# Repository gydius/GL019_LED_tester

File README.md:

# GL019_LED_tester

A simple PCB to test SMD LEDs. Solder your SMD LEDs and add an adaquate resitor to it and you will be able to choose quickly the right couple LED/R for your next project ! 

I did it since I do have quite a lot of references of SMD LEDs in my personnal stock so I would forget what color they are. 

For time for me with sending custom panel to a manufacturer, everything went nice. Used [GitHub - ThisIsNotRocketScience/GerberTools: Tools to load/edit/create/panelizer sets of gerber files](https://github.com/ThisIsNotRocketScience/GerberTools)

# This project is still in progress !

This is the first revision, I got the PCBs from JLC and they're nice !

But there a few mistakes and changes to do for next revision : 

- Change the solderjump for a bigger one.  Might also chage by a 1x2 2.54mm connector and 2.54mm jumper. 

- Get the 0402 and 0804 LEDs on same footprint (and might also add THT LEDs)

- Same but for 0402 and 0804 SMD resistors 

- Increase the maring sikscreen area, it is currently not enough to easily write the LEDs' references on it. 

- Add silkscreen to right S/N off the PCB.

- Change the silkscreen color, the blue is definitey not wise when you want to write on it with black/blue permanent marker. Might try white FR4 with black silkscreen. 

Few photos :

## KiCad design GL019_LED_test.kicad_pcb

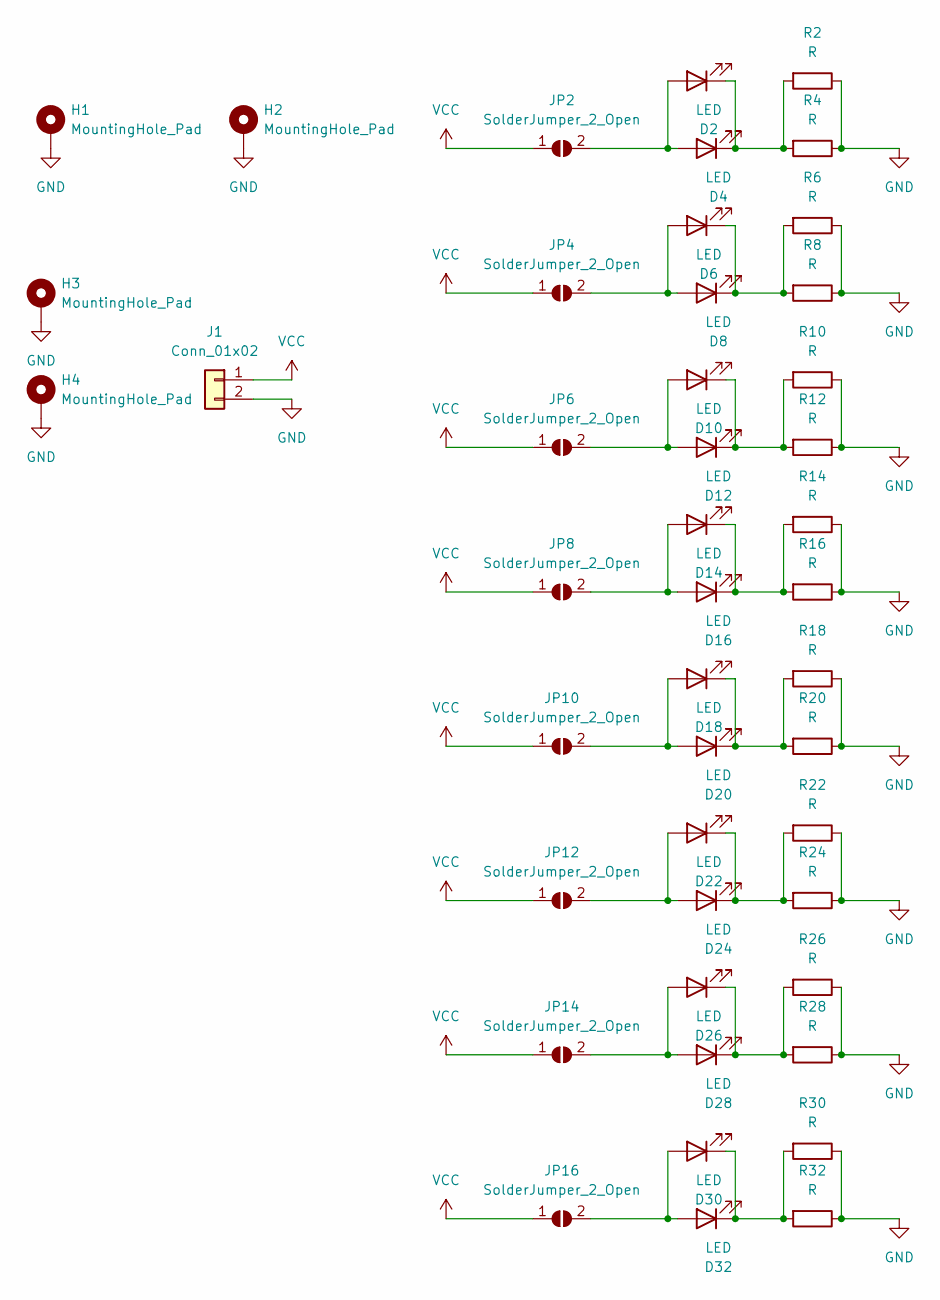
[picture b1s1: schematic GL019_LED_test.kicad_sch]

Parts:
D2, D6, D10, D14, D18, D22, D26, D30: LED; LED_0603_1608Metric_Pad1.05x0.95mm_HandSolder
D4, D8, D12, D16, D20, D24, D28, D32: LED; LED_0805_2012Metric_Pad1.15x1.40mm_HandSolder
H1, H2, H3, H4: MountingHole_Pad; MountingHole_3.2mm_M3_Pad_Via
J1: Conn_01x02; TerminalBlock_bornier-2_P5.08mm
JP2, JP4, JP6, JP8, JP10, JP12, JP14, JP16: SolderJumper_2_Open; SolderJumper-2_P1.3mm_Open_RoundedPad1.0x1.5mm
R2, R6, R10, R14, R18, R22, R26, R30: R; R_0603_1608Metric_Pad0.98x0.95mm_HandSolder
R4, R8, R12, R16, R20, R24, R28, R32: R; R_0805_2012Metric_Pad1.20x1.40mm_HandSolder

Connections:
GND: H1.1, H2.1, H3.1, H4.1, J1.2, R2.1, R4.1, R6.1, R8.1, R10.1, R12.1, R14.1, R16.1, R18.1, R20.1, R22.1, R24.1, R26.1, R28.1, R30.1, R32.1
unnamed: D2.1 (K), D4.1 (K), R2.2, R4.2
unnamed: D2.2 (A), D4.2 (A), JP2.2 (B)
unnamed: D6.1 (K), D8.1 (K), R6.2, R8.2
unnamed: D6.2 (A), D8.2 (A), JP4.2 (B)
unnamed: D10.1 (K), D12.1 (K), R10.2, R12.2
unnamed: D10.2 (A), D12.2 (A), JP6.2 (B)
unnamed: D14.1 (K), D16.1 (K), R14.2, R16.2
unnamed: D14.2 (A), D16.2 (A), JP8.2 (B)
unnamed: D18.1 (K), D20.1 (K), R18.2, R20.2
unnamed: D18.2 (A), D20.2 (A), JP10.2 (B)
unnamed: D22.1 (K), D24.1 (K), R22.2, R24.2
unnamed: D22.2 (A), D24.2 (A), JP12.2 (B)
unnamed: D26.1 (K), D28.1 (K), R26.2, R28.2
unnamed: D26.2 (A), D28.2 (A), JP14.2 (B)
unnamed: D30.1 (K), D32.1 (K), R30.2, R32.2
unnamed: D30.2 (A), D32.2 (A), JP16.2 (B)
VCC: J1.1, JP2.1 (A), JP4.1 (A), JP6.1 (A), JP8.1 (A), JP10.1 (A), JP12.1 (A), JP14.1 (A), JP16.1 (A)

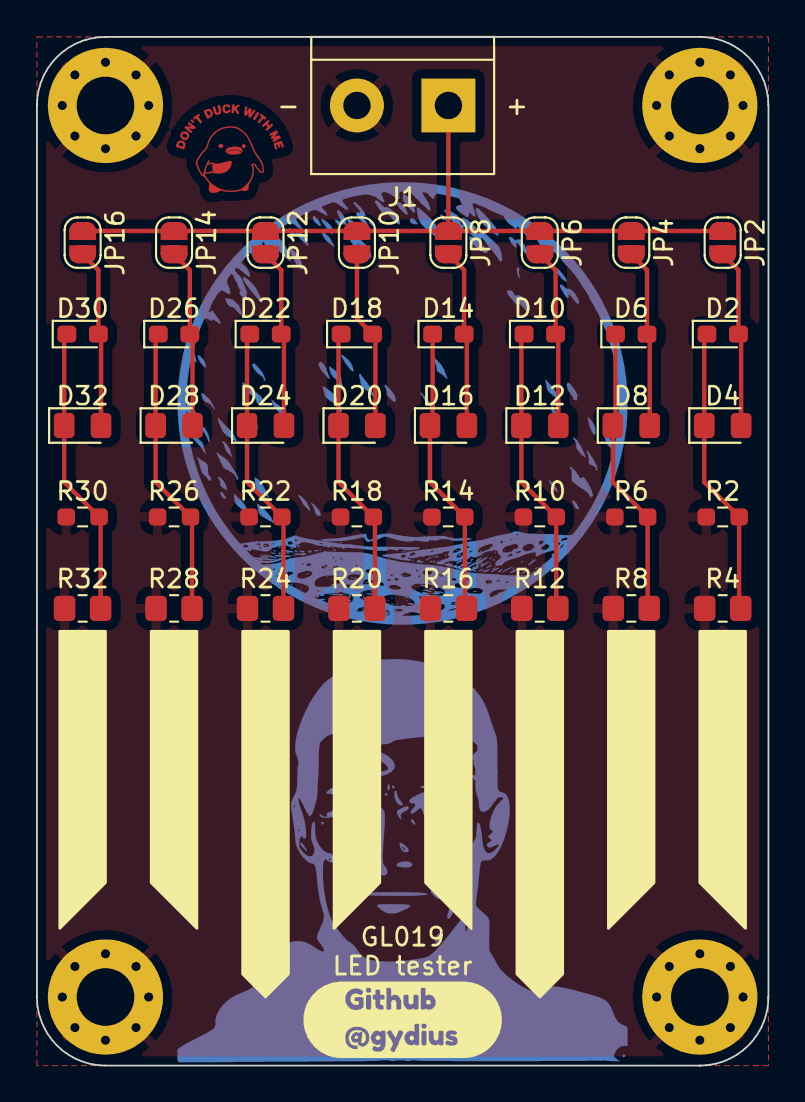
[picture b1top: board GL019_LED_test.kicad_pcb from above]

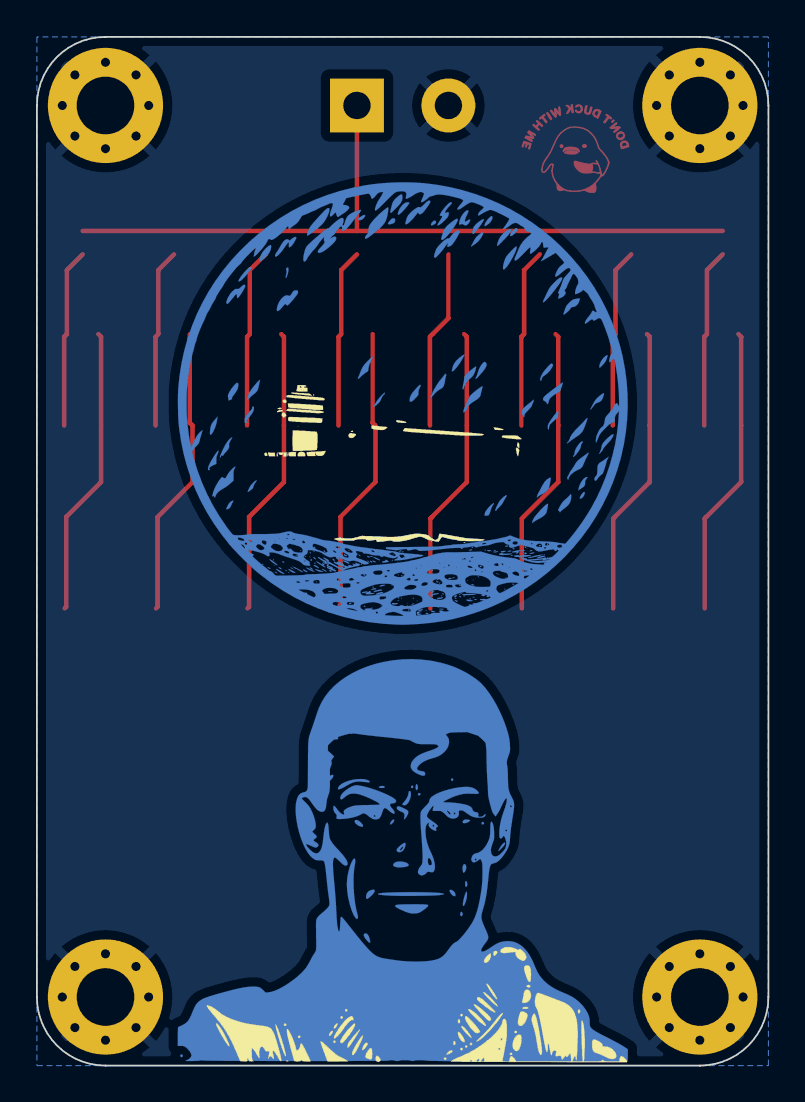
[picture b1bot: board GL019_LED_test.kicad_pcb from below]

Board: 2 copper layers, 40.6 x 57.1 mm, 49 parts (2 on the bottom side), 18 nets.

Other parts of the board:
Ref**: Val**; MoreMoney6mm
Ref**#2: Val**; Duck_banny_2_25mm
Ref**#3: Val**; duck_banny_pcb_25mm
kibuzzard-6320B61E: G***; kibuzzard-6320B61E

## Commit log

2022-10-14 GL019r1
    First revision + readme
2022-10-14 Images fix
    Fix the images on readme
2022-10-15 Images fix
2022-10-15 readme fix
2022-10-15 refix images and readme
